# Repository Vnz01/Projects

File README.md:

# Venz Burgos Projects

**Hardware Projects Content -**

> FPGA Designs

> PCB Designs

> Circuit Design/Analysis

> Software/Hardware Weather App

> Microcontroller Projects

**Software Projects Content -**

> Full Stack Websites

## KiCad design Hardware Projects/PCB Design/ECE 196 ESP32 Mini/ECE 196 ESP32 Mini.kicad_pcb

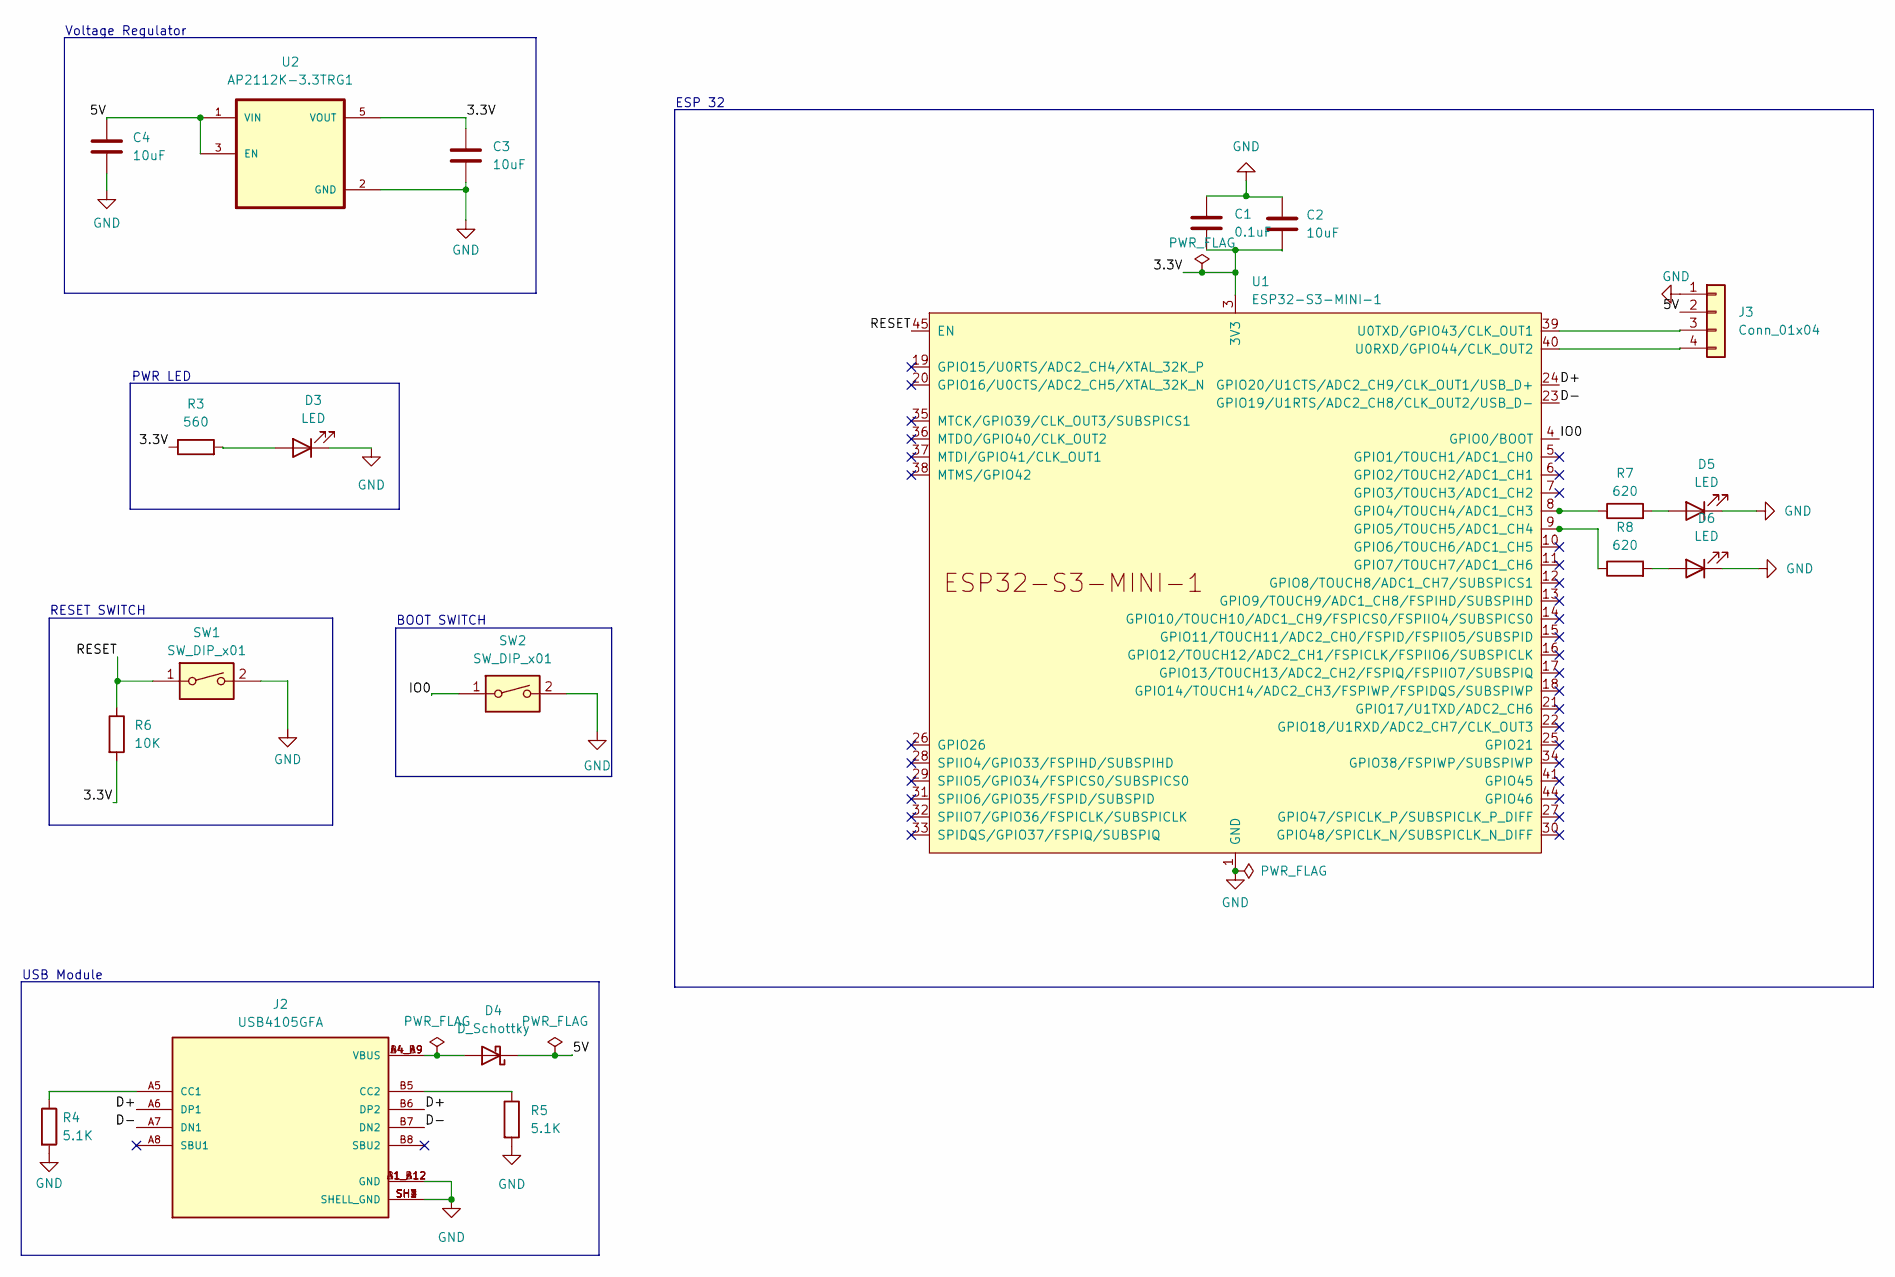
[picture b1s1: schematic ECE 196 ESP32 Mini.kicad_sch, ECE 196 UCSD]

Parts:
C1: 0.1uF; C_0603_1608Metric
C2, C3, C4: 10uF; C_0603_1608Metric
D3, D5, D6: LED; LED_0603_1608Metric_Pad1.05x0.95mm_HandSolder
D4: D_Schottky; D_0805_2012Metric_Pad1.15x1.40mm_HandSolder
J2: USB4105GFA; GCT_USB4105GFA; PARTREV B3
J3: Conn_01x04; PinHeader_1x04_P2.54mm_Vertical
R3: 560; R_0603_1608Metric
R4, R5: 5.1K; R_0603_1608Metric
R6: 10K; R_0603_1608Metric
R7, R8: 620; R_0603_1608Metric
SW1, SW2: SW_DIP_x01; SW_PUSH_6mm
U1: ESP32-S3-MINI-1
U2: AP2112K-3.3TRG1; SOT95P285X140-5N; PARTREV 2-2

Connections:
/3.3V: C1.2, C2.2, C3.1, R3.1, R6.2, U1.3 (3V3), U2.5 (VOUT)
/5V: C4.1, D4.1 (K), J3.2, U2.1 (VIN), U2.3 (EN)
/D+: J2.A6 (DP1), J2.B6 (DP2), U1.24 (GPIO20/U1CTS/ADC2_CH9/CLK_OUT1/USB_D+)
/D-: J2.A7 (DN1), J2.B7 (DN2), U1.23 (GPIO19/U1RTS/ADC2_CH8/CLK_OUT2/USB_D-)
/IO0: SW2.1, U1.4 (GPIO0/BOOT)
/RESET: R6.1, SW1.1, U1.45 (EN)
GND: C1.1, C2.1, C3.2, C4.2, D3.1 (K), D5.1 (K), D6.1 (K), J2.A1_B12 (GND), J2.B1_A12 (GND), J2.SH1 (SHELL_GND), J2.SH2 (SHELL_GND), J2.SH3 (SHELL_GND), J2.SH4 (SHELL_GND), J3.1, R4.2, R5.2, SW1.2, SW2.2, U1.1 (GND), U1.2 (GND), U1.42 (GND), U1.43 (GND), U1.46 (GND), U1.47 (GND), U1.48 (GND), U1.49 (GND), U1.50 (GND), U1.51 (GND), U1.52 (GND), U1.53 (GND), U1.54 (GND), U1.55 (GND), U1.56 (GND), U1.57 (GND), U1.58 (GND), U1.59 (GND), U1.60 (GND), U1.61 (GND), U1.62 (GND), U1.63 (GND), U1.64 (GND), U1.65 (GND), U2.2 (GND)
unnamed: D3.2 (A), R3.2
unnamed: D4.2 (A), J2.A4_B9 (VBUS), J2.B4_A9 (VBUS)
unnamed: D5.2 (A), R7.2
unnamed: D6.2 (A), R8.2
unnamed: J2.A5 (CC1), R4.1
unnamed: J2.B5 (CC2), R5.1
unnamed: J3.3, U1.39 (U0TXD/GPIO43/CLK_OUT1)
unnamed: J3.4, U1.40 (U0RXD/GPIO44/CLK_OUT2)
unnamed: R7.1, U1.8 (GPIO4/TOUCH4/ADC1_CH3)
unnamed: R8.1, U1.9 (GPIO5/TOUCH5/ADC1_CH4)

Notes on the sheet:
BOOT SWITCH
RESET SWITCH
PWR LED
Voltage Regulator
ESP 32
USB Module

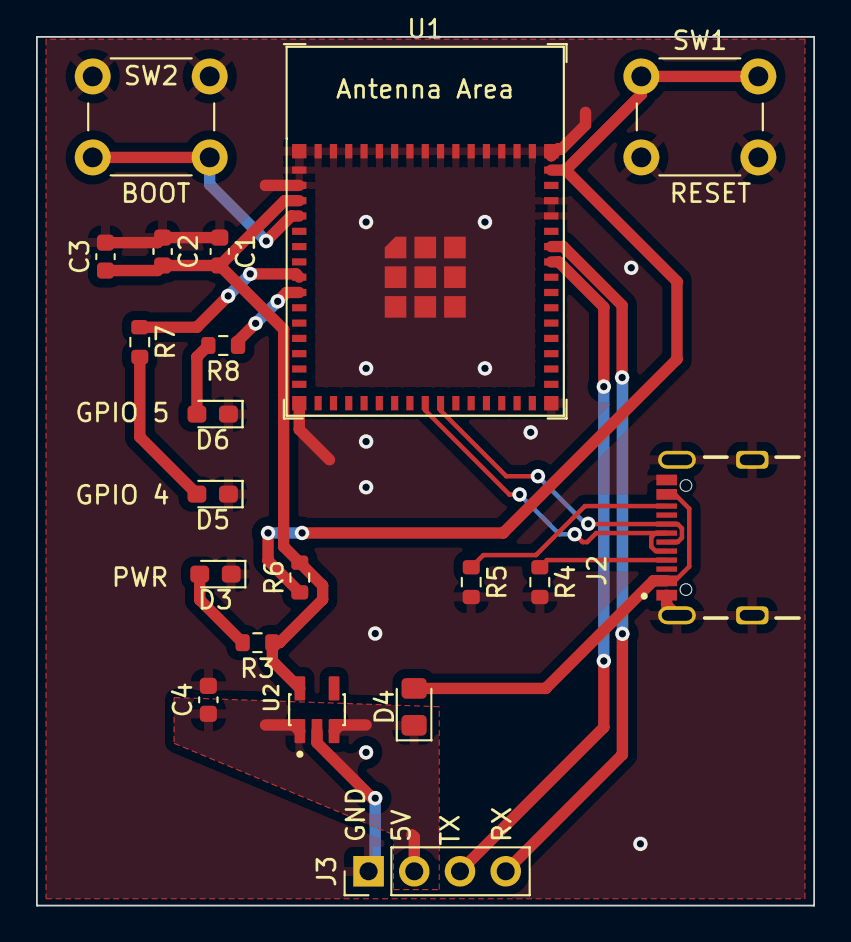
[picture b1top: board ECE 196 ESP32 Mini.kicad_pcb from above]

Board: 2 copper layers, 43.2 x 48.3 mm, 20 parts (0 on the bottom side), 17 nets.

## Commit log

2023-03-12 Project Update 1
2023-03-12 Project Update 1.1
2023-03-12 Project Update 1.2
2023-03-12 Project Update 1.3
2023-03-13 ReadME File
2023-03-13 Project Update 1.4
2023-03-28 Update 1
2023-05-02 Hardware/Software Project Weather App added
2023-05-02 Microcontroller Project Added
2023-05-14 Updated Resume
2023-05-22 New Projects MCU & PCB Design
2023-12-21 Newest changes for E4E added PCB
2023-12-21 ADDED GITIGNORE
2023-12-21 Added Motor Driver Controller Pic
